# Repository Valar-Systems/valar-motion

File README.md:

# Valar Motion — Valar Systems motor controllers

The easiest, fastest, cheapest, and safest way to spin a stepper motor
**wirelessly**. Valar Motion is a family of tiny Wi-Fi stepper controllers built
around a Trinamic **TMC2209** driver — precisely control a motor's distance,
speed, current, and stall behaviour within minutes of unboxing, from any browser,
with no Home Assistant required.

All three boards share the same TMC2209 driver, a synchronous DC/DC converter,
three buttons, end-stop inputs, and a USB-C port for flashing. They differ only
in the microcontroller and — on the 3101 — an onboard magnetic encoder.

| Board | MCU | Radios | Extra | Price |
|-------|-----|--------|-------|-------|
| **VAL3000** | ESP32-C3 | Wi-Fi | — | $34.99 |
| **VAL3100** | ESP32-C6 | Wi-Fi / Thread / Zigbee / Matter / BLE | Status LED | $44.99 |
| **VAL3101** | ESP32-C6 | Wi-Fi / Thread / Zigbee / Matter / BLE | Status LED + AS5600 encoder (closed-loop) | $54.99 |

Buy them at [valarsystems.com](https://valarsystems.com). Sold out? Hit the
"Notify me when available" button — that's the only way we know to make more.

## What's on the board

The board packs a full wireless stepper controller into a footprint that bolts
onto the back of a **NEMA 17** motor (the four mounting holes line up with the
motor face):

- **Espressif ESP32** — Wi-Fi microcontroller with native USB (C3 on the VAL3000;
  C6 with Thread/Zigbee/Matter/BLE on the VAL3100/3101)
- **Trinamic TMC2209** stepper driver — silent StealthChop + sensorless StallGuard
- **5–24 V synchronous DC/DC converter** — efficient on-board regulation from the
  motor supply, no separate logic power needed
- **Three buttons** for manual open / close / Wi-Fi-reset
- **Motor hookup** — the **VAL3100 / VAL3101** ship with a **4-pin screw terminal
  pre-soldered** for the stepper (alongside the JST-XH); the **VAL3000** has the
  **JST-XH** connector (screw terminal included to solder on, or wire directly to
  the pads)
- **Power** — 2.1 × 5.5 mm barrel **and** a 2-pin screw terminal, plus **USB-C**
  for flashing
- **Reverse-polarity protection** on the **VAL3100 / VAL3101** (the VAL3000 has
  none — mind the polarity)

<p align="center">
  
  <br>
  <em>Board anatomy (VAL3000 shown; the VAL3100/3101 share the same layout on an ESP32-C6).</em>
</p>

## Quick start

Setup takes about three minutes:

1. Connect any bipolar (4-wire) stepper motor.
2. Connect a 12–24 V, 2 A+ power supply (2.1 × 5.5 mm barrel, **center positive**).
3. Press one of the buttons — the motor starts and stops.

That's it. When you're ready to customize, plug in USB-C and flash a build below.

> **⚠️ VAL3000 only:** the VAL3000 has **no reverse-polarity protection** —
> double-check your supply is center-positive before powering on. The
> VAL3100 / VAL3101 add reverse-polarity protection.

## Flash a board (the fast way)

The board ships bare. Grab the prebuilt binary for your board from the
[latest release](../../releases/latest) and flash it from your browser at
[web.esphome.io](https://web.esphome.io) with a USB-C cable — no toolchain, no
soldering, no Home Assistant required. On first boot the board makes its own
Wi-Fi hotspot; connect, join it to your network, and control it from any
browser. It's discoverable in Home Assistant over the ESPHome API too.

> First-time flashing note: the USB-C port connects straight to the ESP32 (USB
> CDC — no USB-to-UART bridge). If the board isn't detected on a brand-new unit,
> enter download mode manually: **hold** BOOT, **tap** RESET, then **release**
> BOOT. After the first upload this is automatic.

## Build from source

```bash
python3 -m venv venv && source venv/bin/activate
pip install esphome
cp secrets.example.yaml secrets.yaml     # not needed for a bare flash

esphome compile boards/val3100/val3100.yaml
# → factory image at:
#   boards/val3100/.esphome/build/val3100/.pioenvs/val3100/firmware.factory.bin
```

Swap `val3100` for `val3000` or `val3101`. CI
(`.github/workflows/build-firmware.yml`) builds all three on every push and
attaches `*.factory.bin` / `*.ota.bin` to tagged releases.

## Firmware updates (OTA)

Boards can update themselves over Wi-Fi — no computer needed — by fetching the
newest release asset for their board. **Release asset names are an API**: keep
`val3000.factory.bin`, `val3100.ota.bin`, etc. stable so units already in the
field keep updating after any repo move. See `docs/MIGRATION.md`.

## Detailed features

### Trinamic TMC2209 + StallGuard

The TMC2209 is one of the best stepper drivers on the market — feature-rich yet
affordable, with silent StealthChop operation and sensorless stall detection.
**StallGuard** stops the motor whenever the load exceeds a threshold you set — no
limit switches needed — which makes the board safe for curtains, windows, blinds,
and anything that could pinch or jam. The driver is controlled over a single-wire
UART, so speed, current, microstepping, and stall sensitivity are all tunable
live from the web UI.

### Flexible motor connector

Connect a motor three ways: the on-board 4-pin JST-XH plug, the included 4-pin
screw terminal (solder it to the exposed pins), or by soldering the motor wires
directly to the board.

### USB-C + three buttons

Flash firmware and monitor serial over USB-C — no programmer needed. Three
on-board buttons give physical open / close control plus a Wi-Fi reset, handy for
products built on the board (our Ropener curtain opener uses exactly this).

## Repository layout

```
valar-motion/
├── boards/
│   ├── val3000/val3000.yaml   # ESP32-C3 pin map + substitutions
│   ├── val3100/val3100.yaml   # ESP32-C6 + status LED
│   └── val3101/val3101.yaml   # ESP32-C6 + status LED + AS5600 encoder
├── common/
│   └── valar-core.yaml        # shared, board-independent behaviour
├── hardware/                  # PCB, schematics, libraries (per board)
├── docs/                      # datasheets, guides, media
└── .github/workflows/         # CI: builds a factory + OTA bin per board
```

The important idea: **behaviour lives in `common/valar-core.yaml`**, which every
board pulls in as a package. Each `boards/<board>/<board>.yaml` is a thin wrapper
that only sets that board's chip, GPIO pin map, and OTA asset name. Change the
core once and all three boards inherit it.

## Hardware & documentation

- **Hardware guide:** [`docs/hardware-guide.md`](docs/hardware-guide.md) — power/voltage/current/heat, driving the TMC2209 (UART vs STEP/DIR), and mounting to a NEMA 17
- **PCB / KiCad sources:** [`hardware/val3000`](hardware/val3000),
  [`hardware/val3100`](hardware/val3100) (the VAL3101 uses the VAL3100 board with
  the AS5600 encoder populated — see [`hardware/val3101`](hardware/val3101))
- **Schematic (PDF):** [`docs/val3000/schematic.pdf`](docs/val3000/schematic.pdf)
- **Trinamic book (PDF):** [`docs/val3000/Trinamic_Book_V4.pdf`](docs/val3000/Trinamic_Book_V4.pdf) — in-depth guide to Trinamic drivers
- **TMC2209 datasheet:** [analog.com](https://www.analog.com/media/en/technical-documentation/data-sheets/tmc2209_datasheet_rev1.09.pdf)

## Applications

This repo is the **board firmware**. Products built on these boards live in their
own repos and layer their behaviour on top of `common/valar-core.yaml` — e.g.
[The Ropener](https://github.com/Valar-Systems/Ropener), a smart curtain opener,
which adds cover/position logic and homing on the same boards.

## License

Licensed under the [CERN Open Hardware Licence Version 2 — Strongly Reciprocal](LICENSE).

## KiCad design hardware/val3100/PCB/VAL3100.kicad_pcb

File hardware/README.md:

# Hardware

PCB source, schematics, and libraries for each board we sell, one folder per board.

    hardware/val3000/   # ESP32-C3 board — KiCad source + libraries (from the old VAL3000 repo)
    hardware/val3100/   # ESP32-C6 board — KiCad source + libraries (from the old VAL3100 repo)
    hardware/val3101/   # ESP32-C6 + AS5600 — SAME PCB as val3100 (see below)

Board-specific documentation (schematic PDFs, datasheets, media) lives under
`docs/<board>/` — e.g. `docs/val3000/`.

## VAL3101 shares the VAL3100 board

The **VAL3101 is not a separate PCB** — it is the VAL3100 board with the AS5600
magnetic encoder **populated**. The VAL3100 layout already carries the AS5600
footprint and its I²C routing; on a plain VAL3100 the chip is simply left
unstuffed. Populate it (plus the shaft magnet) and it becomes a VAL3101.

So `hardware/val3101/` intentionally has no separate KiCad project — use
`hardware/val3100/`. The encoder's I²C pins, read from that schematic, are
**SDA = GPIO14, SCL = GPIO15** (see `boards/val3101/val3101.yaml`).

## What was migrated

Only real design source was brought over: `.kicad_pcb`, `.kicad_sch`,
`.kicad_pro`, vendor `Libraries/`, and fabrication config. KiCad auto-save
`*-backups/` archives, project-local `.kicad_prl` state, lock files, and caches
were intentionally left out (and are `.gitignore`d) — they remain in the
original board repos, which are archived rather than deleted.

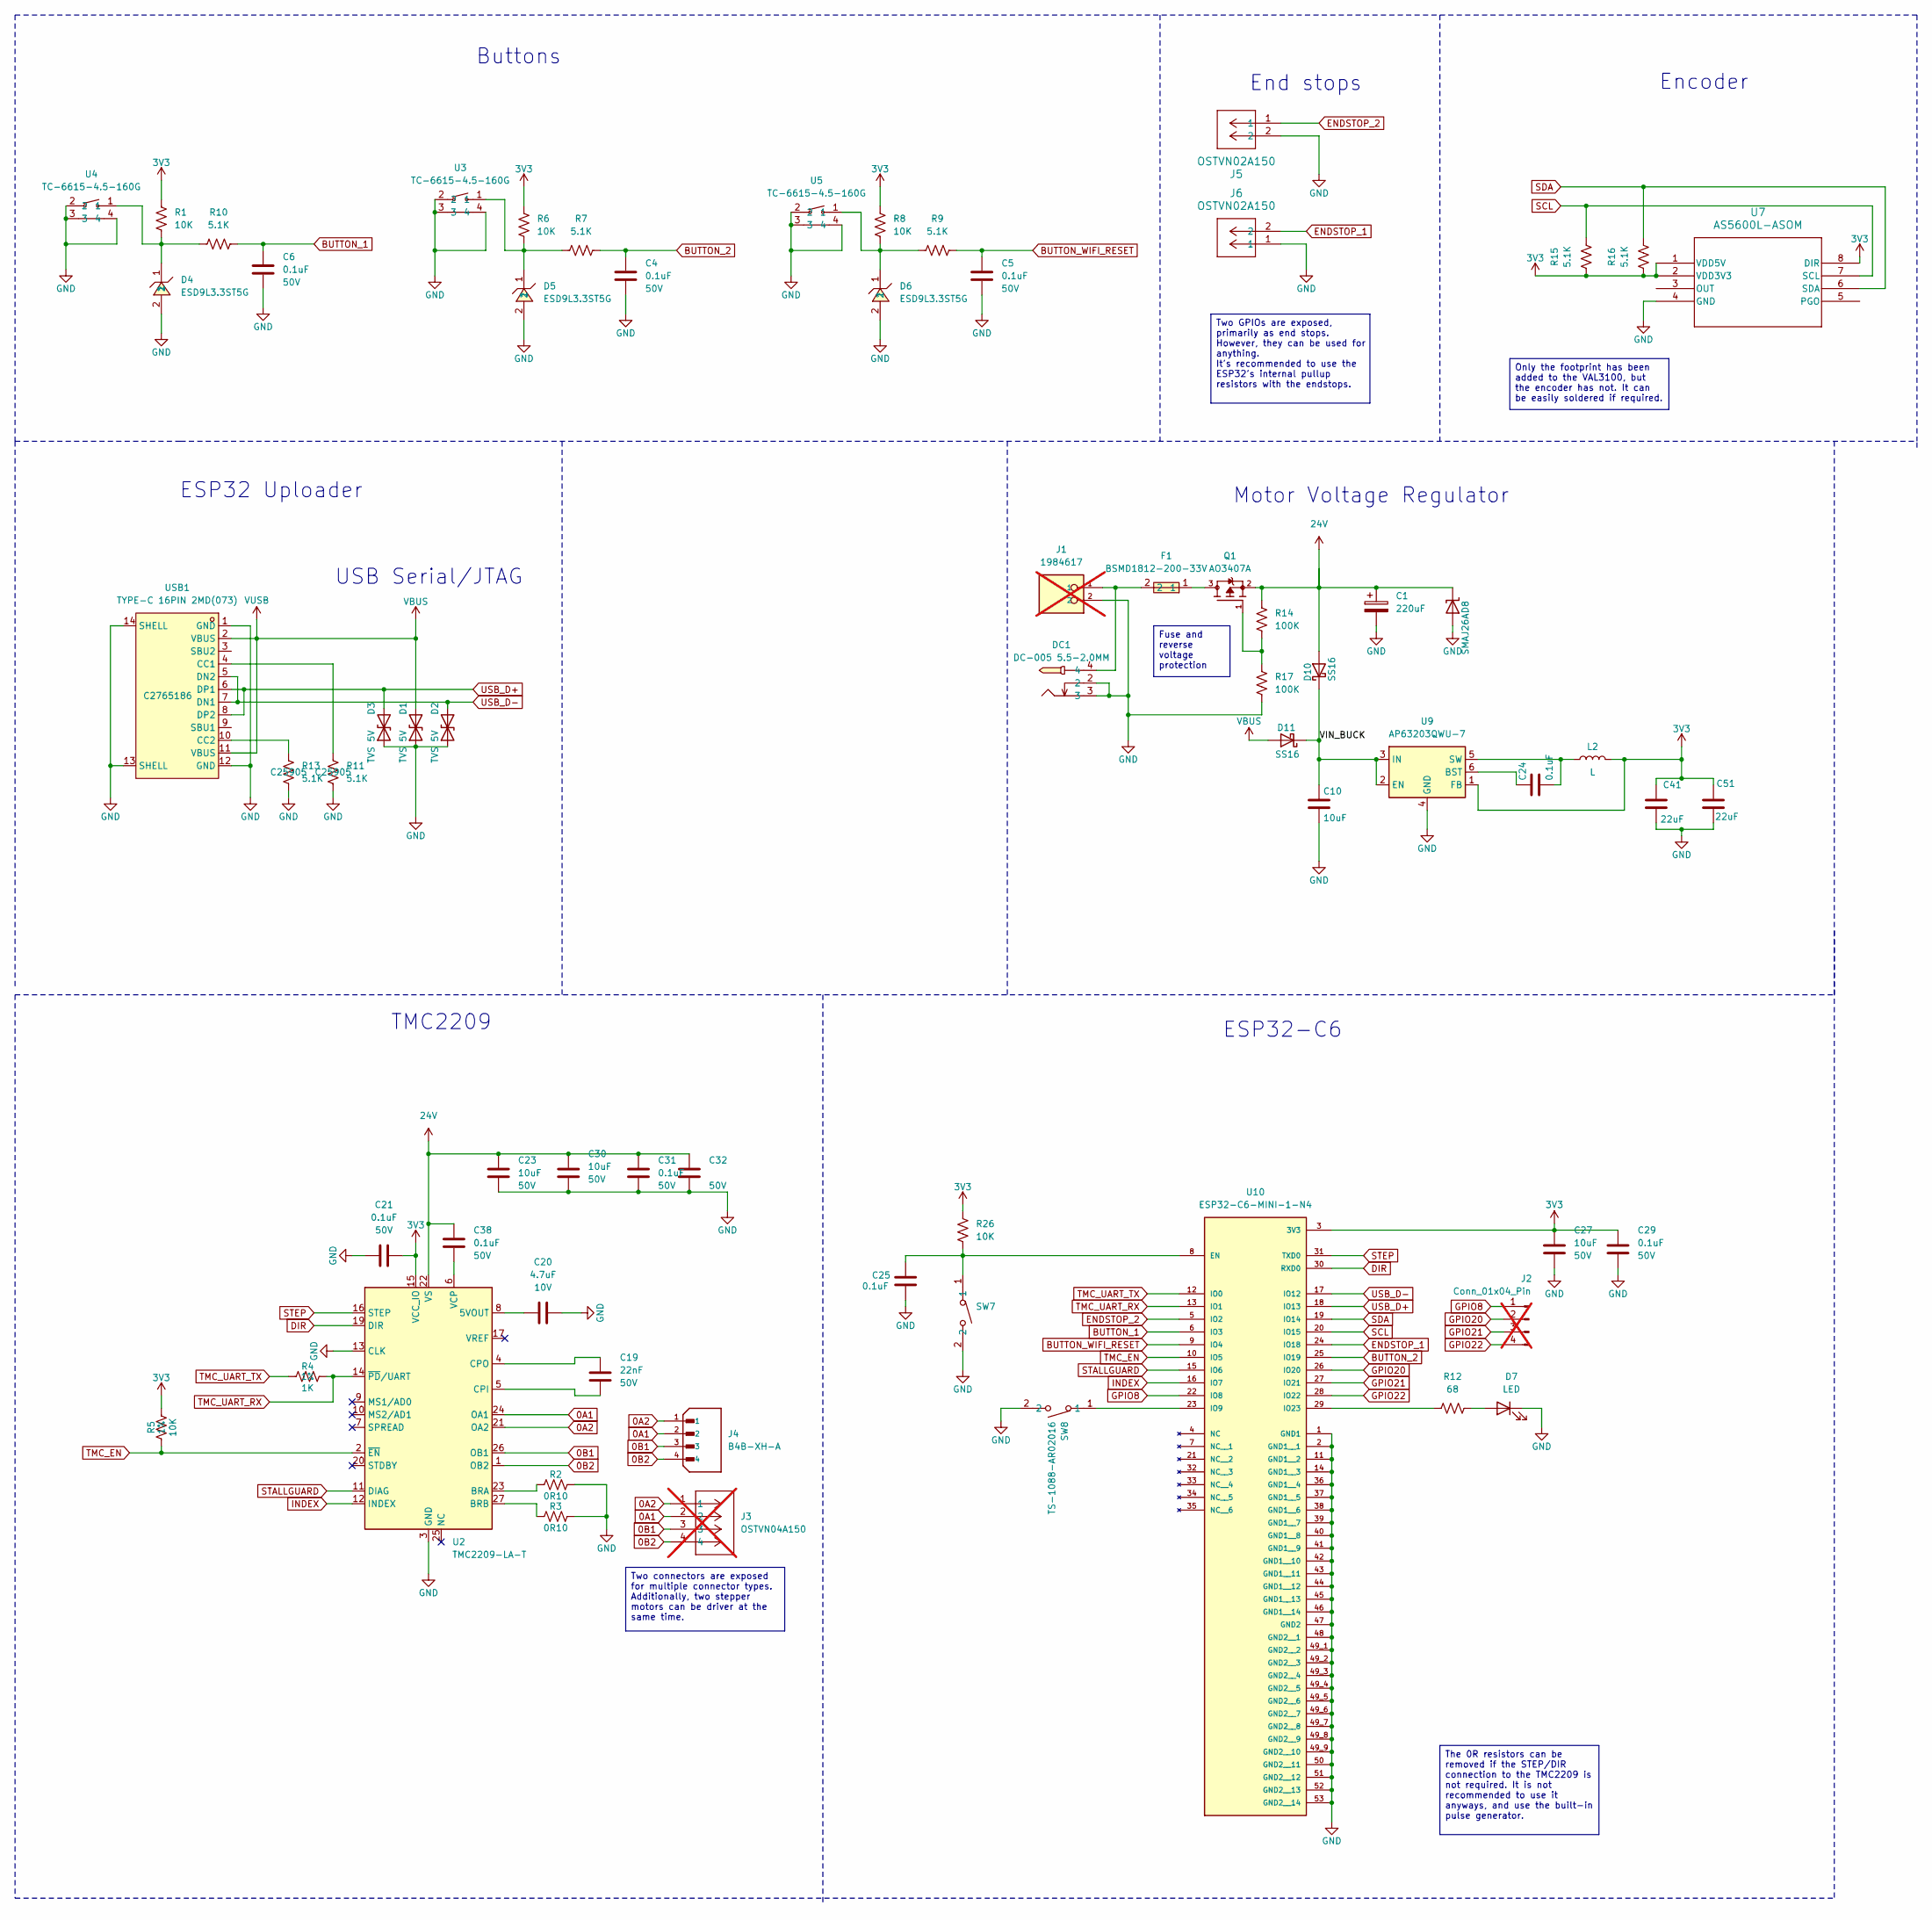
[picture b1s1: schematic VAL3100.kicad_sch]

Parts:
C1: 220uF; CAP-SMD_BD10.0-L10.3-W10.3-LS11.3-FD; Voltage 50V; LCSC C98743
C4, C5, C6, C21, C24, C29, C31, C32, C38: 0.1uF; C_0402_1005Metric; Voltage 50V; Tolerance 10%; LCSC C77020
C10: 10uF; C_0805_2012Metric; Voltage 50V; Tolerance 10%; LCSC C440198
C19: 22nF; C_0402_1005Metric; Voltage 50V; Tolerance 10%; LCSC C1532
C20: 4.7uF; C_0402_1005Metric; Voltage 10V; Tolerance 10%; LCSC C23733
C23, C27, C30: 10uF; C_0805_2012Metric; Voltage 50V; Tolerance 20%; LCSC C440198
C25: 0.1uF; C_0402_1005Metric; Voltage 50V; LCSC C77020
C41, C51: 22uF; C_0603_1608Metric; Voltage 10V; Tolerance 20%; LCSC C86295
D1, D2, D3: SOD-523_BSD5C051L; D_SOD-523; MPN BSD5C051L; LCSC C151983
D4, D5, D6: ESD9L3.3ST5G; SOD-923_L0.8-W0.6-LS1.0-RD; LCSC C233387
D7: LED; LED_0603_1608Metric; LCSC C2286
D8: SMAJ26A; D_SMA; MPN SMAJ26A-TR; LCSC C132945
D10, D11: SS16; D_SMA; MPN SS16; LCSC C22452
DC1: DC-005 5.5-2.0MM; DC-IN-TH_DC-005-5.5-2.0; LCSC C16214
F1: BSMD1812-200-33V; F1812; LCSC C7433877
J1: 1984617; PHOENIX_1984617; PARTREV 22.08.2018; LCSC C695629; not fitted
J2: Conn_01x04_Pin; PinHeader_1x04_P2.54mm_Vertical; not fitted
J3: OSTVN04A150; CONN_OSTVN04A150_OST; JLCPCB C918122; not fitted
J4: B4B-XH-A; JST_B4B-XH-A; PARTREV 7/4/21; LCSC C144395
J5, J6: OSTVN02A150; CONN_OSTVN02A150_OST
L2: L; IND-SMD_L3.0-W3.0_FNR30XXS; LCSC C48020
Q1: AO3407A; SOT95P280X125-3N; PARTREV 5; LCSC C15155
R1, R5, R6, R8, R26: 10K; R_0402_1005Metric; LCSC C25744
R2, R3: 0R10; C_0805_2012Metric; LCSC C2074770
R4: 1K; R_0402_1005Metric; LCSC C11702
R7, R9, R10, R11, R13, R15, R16: 5.1K; R_0402_1005Metric; LCSC C25905
R12: 68; R_0402_1005Metric; LCSC C25131
R14, R17: 100K; R_0402_1005Metric; LCSC C25741
SW7, SW8: TS-1088-AR02016; SW-SMD_L3.9-W3.0-P4.45; LCSC C720477
U2: TMC2209-LA-T; VQFN-28-1EP_5x5mm_P0.5mm_EP3.7x3.7mm_ThermalVias; LCSC C2150710
U3, U4, U5: TC-6615-4.5-160G; KEY-TH_TC-6615-4.5-160G; LCSC C6575012
U7: AS5600L-ASOM; AS5600L-ASOM_AMS; LCSC C2153666
U9: AP63203QWU-7; TSOT-23-6; LCSC C780769
U10: ESP32-C6-MINI-1-N4; XCVR_ESP32-C6-MINI-1-N4; PARTREV 1.0; DigiKey_Part_Number 1965-ESP32-C6-MINI-1-N4CT-ND
USB1: TYPE-C 16PIN 2MD(073); USB-C-SMD_TYPE-C-6PIN-2MD-073; LCSC C2765186

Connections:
0A1: J3.2, J4.2, U2.24 (OA1)
0A2: J3.1, J4.1, U2.21 (OA2)
0B1: J3.3, J4.3, U2.26 (OB1)
0B2: J3.4, J4.4, U2.1 (OB2)
3V3: C21.2, C27.1, C29.1, C41.2, C51.2, L2.2, R1.1, R5.2, R6.1, R8.1, R15.1, R16.1, R26.1, U2.15 (VCC_IO), U7.1 (VDD5V), U7.2 (VDD3V3), U7.8 (DIR), U9.1 (FB), U10.3 (3V3)
24V: C1.1, C23.1, C30.1, C31.2, C32.2, C38.2, D8.1 (K), D10.2 (A), Q1.2, R14.2, U2.22 (VS), U2.28 (VS)
/VIN_BUCK: C10.1, D10.1 (K), D11.1 (K), U9.2 (EN), U9.3 (IN)
BUTTON_1: C6.2, R10.2, U10.6 (IO3)
BUTTON_2: C4.2, R7.2, U10.25 (IO19)
BUTTON_WIFI_RESET: C5.2, R9.2, U10.9 (IO4)
DIR: U2.19 (DIR), U10.30 (RXD0)
ENDSTOP_1: J6.2, U10.24 (IO18)
ENDSTOP_2: J5.1, U10.5 (IO2)
GND: C1.2, C4.1, C5.1, C6.1, C10.2, C20.2, C21.1, C23.2, C25.2, C27.2, C29.2, C30.2, C31.1, C32.1, C41.1, C51.1, D1.1 (A1), D2.1 (A1), D3.1 (A1), D4.2, D5.2, D6.2, D7.1 (K), D8.2 (A), DC1.2, DC1.3, J1.2, J5.2, J6.1, R2.2, R3.2, R11.2, R13.1, R17.1, SW7.2, SW8.2, U2.3 (GND), U2.13 (CLK), U2.18 (GND), U2.29 (GND), U3.2, U3.3, U3.4, U4.2, U4.3, U4.4, U5.2, U5.3, U5.4, U7.4 (GND), U9.4 (GND), U10.1 (GND1), U10.2 (GND1__1), U10.11 (GND1__2), U10.14 (GND1__3), U10.36 (GND1__4), U10.37 (GND1__5), U10.38 (GND1__6), U10.39 (GND1__7), U10.40 (GND1__8), U10.41 (GND1__9), U10.42 (GND1__10), U10.43 (GND1__11), U10.44 (GND1__12), U10.45 (GND1__13), U10.46 (GND1__14), U10.47 (GND2), U10.48 (GND2__1), U10.49_1 (GND2__2), U10.49_2 (GND2__3), U10.49_3 (GND2__4), U10.49_4 (GND2__5), U10.49_5 (GND2__6), U10.49_6 (GND2__7), U10.49_7 (GND2__8), U10.49_8 (GND2__9), U10.49_9 (GND2__10), U10.50 (GND2__11), U10.51 (GND2__12), U10.52 (GND2__13), U10.53 (GND2__14), USB1.1 (GND), USB1.12 (GND), USB1.13 (SHELL), USB1.14 (SHELL); also elsewhere on the board
GPIO8: J2.1, U10.22 (IO8)
GPIO20: J2.2, U10.26 (IO20)
GPIO21: J2.3, U10.27 (IO21)
GPIO22: J2.4, U10.28 (IO22)
INDEX: U2.12 (INDEX), U10.16 (IO7)
unnamed: D4.1, R1.2, R10.1, U4.1
unnamed: D5.1, R6.2, R7.1, U3.1
unnamed: D6.1, R8.2, R9.1, U5.1
unnamed: D7.2 (A), R12.2
unnamed: DC1.4, F1.2, J1.1
unnamed: F1.1, Q1.3
unnamed: Q1.1, R14.1, R17.2
unnamed: C20.1, U2.8 (5VOUT)
unnamed: R2.1, U2.23 (BRA)
unnamed: R3.1, U2.27 (BRB)
unnamed: C19.2, U2.5 (CPI)
unnamed: C19.1, U2.4 (CPO)
unnamed: C38.1, U2.6 (VCP)
unnamed: C24.1, U9.6 (BST)
unnamed: C24.2, L2.1, U9.5 (SW)
unnamed: C25.1, R26.2, SW7.1, U10.8 (EN)
unnamed: SW8.1, U10.23 (IO9)
unnamed: R12.1, U10.29 (IO23)
unnamed: R11.1, USB1.4 (CC1)
unnamed: R13.2, USB1.10 (CC2)
SCL: R15.2, U7.7 (SCL), U10.20 (IO15)
SDA: R16.2, U7.6 (SDA), U10.19 (IO14)
STALLGUARD: U2.11 (DIAG), U10.15 (IO6)
STEP: U2.16 (STEP), U10.31 (TXD0)
TMC_EN: R5.1, U2.2 (~EN), U10.10 (IO5)
TMC_UART_RX: R4.2, U2.14 (~PD/UART), U10.13 (IO1)
TMC_UART_TX: R4.1, U10.12 (IO0)
USB_D+: D3.2 (A2), U10.18 (IO13), USB1.6 (DP1), USB1.8 (DP2)
USB_D-: D2.2 (A2), U10.17 (IO12), USB1.5 (DN2), USB1.7 (DN1)
VBUS: D1.2 (A2), D11.2 (A), USB1.2 (VBUS), USB1.11 (VBUS)

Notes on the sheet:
Motor Voltage Regulator
ESP32-C6
Buttons
TMC2209
ESP32 Uploader
End stops
Encoder
USB Serial/JTAG
The 0R resistors can be removed if the STEP/DIR connection to the TMC2209 is not required. It is not recommended to use it anyways, and use the built-in pulse generator.
Two connectors are exposed for multiple connector types. Additionally, two stepper motors can be driver at the same time.
Only the footprint has been added to the VAL3100, but the encoder has not. It can be easily soldered if required.
Two GPIOs are exposed, primarily as end stops. However, they can be used for anything. It's recommended to use the ESP32's internal pullup resistors with the endstops.
Fuse and reverse voltage protection

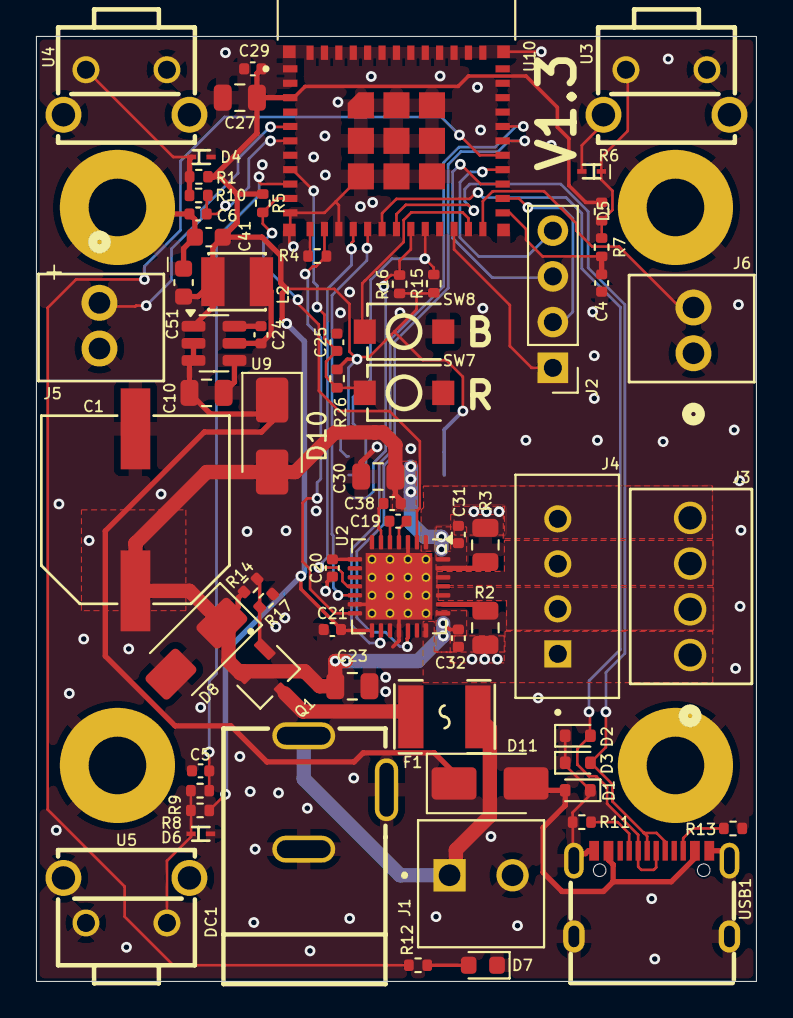
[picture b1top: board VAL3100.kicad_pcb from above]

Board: 4 copper layers, 40.0 x 52.5 mm, 71 parts (1 on the bottom side), 49 nets.

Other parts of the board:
H1, H2, H3, H4: MountingHole_3.2mm_M3_Pad

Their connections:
GND: H1.1, H2.1, H3.1, H4.1; also elsewhere on the board

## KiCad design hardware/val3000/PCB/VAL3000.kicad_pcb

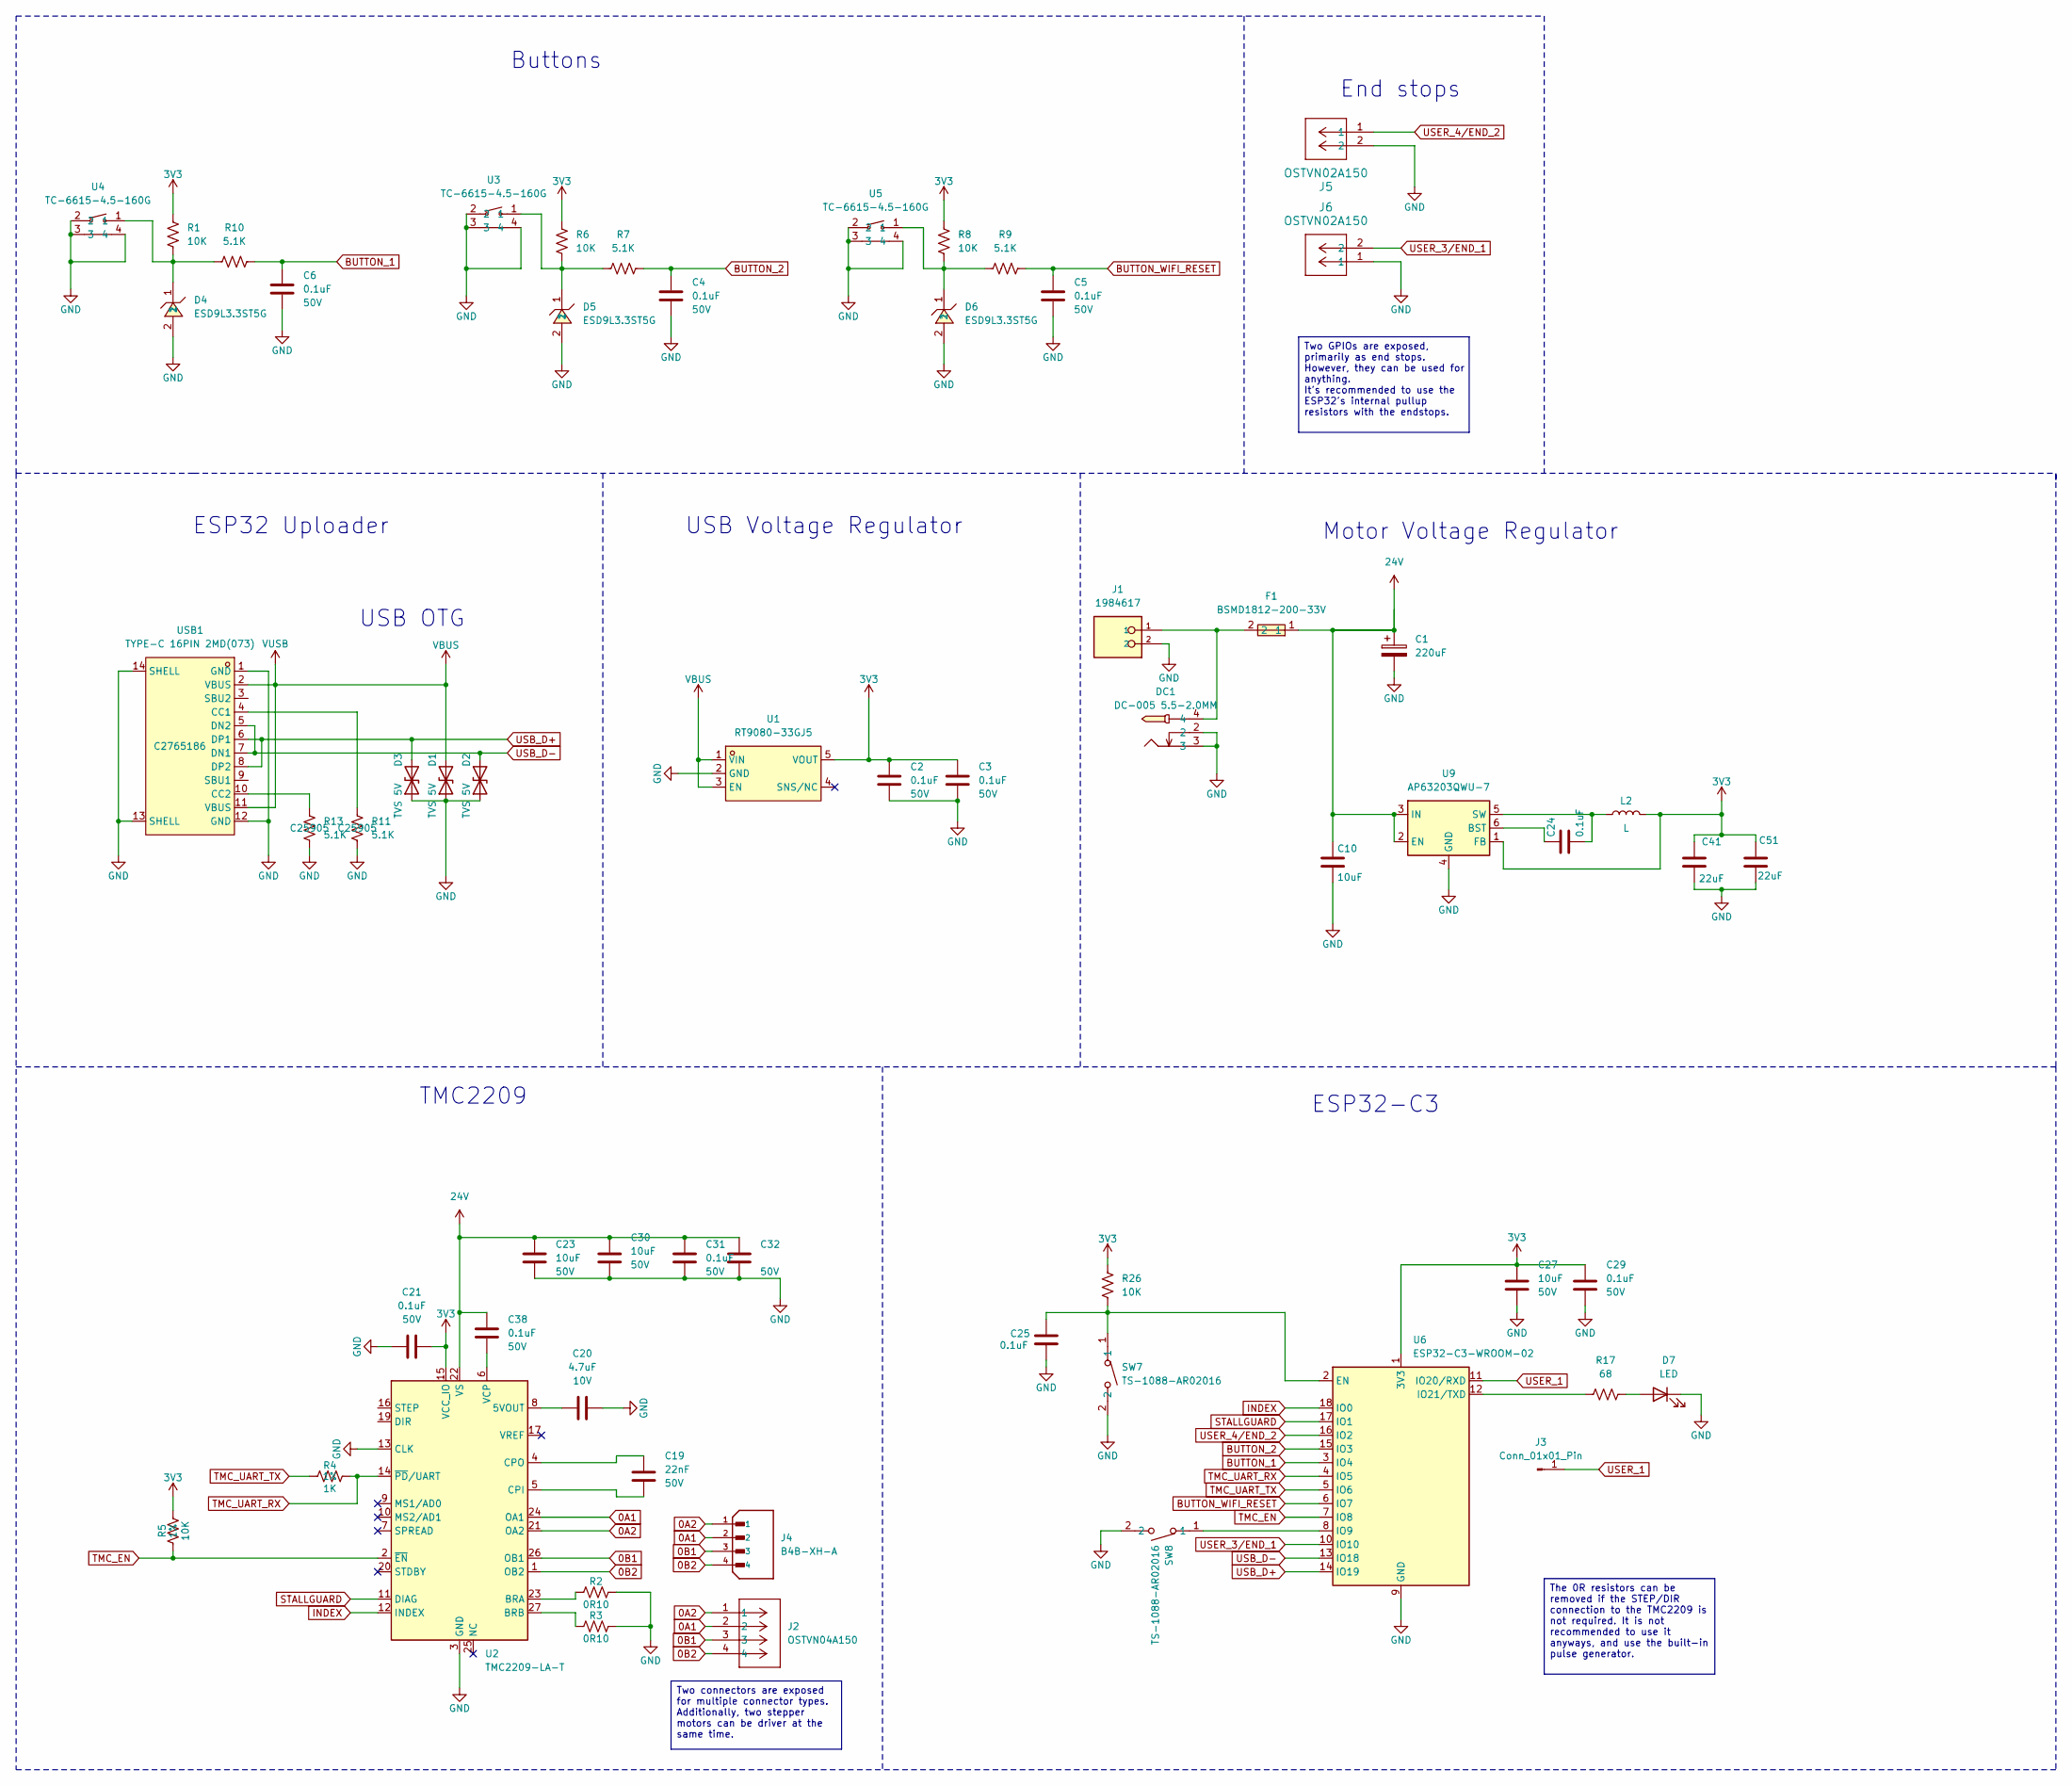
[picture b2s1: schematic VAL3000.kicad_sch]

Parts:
C1: 220uF; CAP-SMD_BD10.0-L10.3-W10.3-LS11.3-FD; Voltage 50V; LCSC C98743
C2, C3, C4, C5, C6, C21, C24, C29, C31, C32, C38: 0.1uF; C_0402_1005Metric; Voltage 50V; Tolerance 10%; LCSC C77020
C10: 10uF; C_0805_2012Metric; Voltage 50V; Tolerance 10%; LCSC C440198
C19: 22nF; C_0402_1005Metric; Voltage 50V; Tolerance 10%; LCSC C1532
C20: 4.7uF; C_0402_1005Metric; Voltage 10V; Tolerance 10%; LCSC C23733
C23, C27, C30: 10uF; C_0805_2012Metric; Voltage 50V; Tolerance 20%; LCSC C440198
C25: 0.1uF; C_0402_1005Metric; Voltage 50V; LCSC C77020
C41, C51: 22uF; C_0603_1608Metric; Voltage 10V; Tolerance 20%; LCSC C86295
D1, D2, D3: SOD-523_BSD5C051L; D_SOD-523; MPN BSD5C051L; LCSC C151983
D4, D5, D6: ESD9L3.3ST5G; SOD-923_L0.8-W0.6-LS1.0-RD; LCSC C233387
D7: LED; LED_0603_1608Metric; LCSC C2286
DC1: DC-005 5.5-2.0MM; DC-IN-TH_DC-005-5.5-2.0; LCSC C16214
F1: BSMD1812-200-33V; F1812; LCSC C7433877
J1: 1984617; PHOENIX_1984617; PARTREV 22.08.2018; LCSC C695629
J2: OSTVN04A150; CONN_OSTVN04A150_OST; JLCPCB C918122
J3: Conn_01x01_Pin
J4: B4B-XH-A; JST_B4B-XH-A; PARTREV 7/4/21; LCSC C144395
J5, J6: OSTVN02A150; CONN_OSTVN02A150_OST
L2: L; IND-SMD_L3.0-W3.0_FNR30XXS; LCSC C48020
R1, R5, R6, R8, R26: 10K; R_0402_1005Metric; LCSC C25744
R2, R3: 0R10; C_0805_2012Metric; LCSC C2074770
R4: 1K; R_0402_1005Metric; LCSC C11702
R7, R9, R10, R11, R13: 5.1K; R_0402_1005Metric; LCSC C25905
R17: 68; R_0402_1005Metric; LCSC C25131
SW7, SW8: TS-1088-AR02016; SW-SMD_L3.9-W3.0-P4.45; LCSC C720477
U1: RT9080-33GJ5; TSOT-23-5_L2.9-W1.6-P0.95-LS2.8-BL; LCSC C841192
U2: TMC2209-LA-T; VQFN-28-1EP_5x5mm_P0.5mm_EP3.7x3.7mm_ThermalVias; LCSC C2150710
U3, U4, U5: TC-6615-4.5-160G; KEY-TH_TC-6615-4.5-160G; LCSC C6575012
U6: ESP32-C3-WROOM-02; LCSC C2934560
U9: AP63203QWU-7; TSOT-23-6; LCSC C780769
USB1: TYPE-C 16PIN 2MD(073); USB-C-SMD_TYPE-C-6PIN-2MD-073; LCSC C2765186

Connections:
0A1: J2.2, J4.2, U2.24 (OA1)
0A2: J2.1, J4.1, U2.21 (OA2)
0B1: J2.3, J4.3, U2.26 (OB1)
0B2: J2.4, J4.4, U2.1 (OB2)
3V3: C2.2, C3.2, C21.2, C27.1, C29.1, C41.2, C51.2, L2.2, R1.1, R5.2, R6.1, R8.1, R26.1, U1.5 (VOUT), U2.15 (VCC_IO), U6.1 (3V3), U9.1 (FB)
24V: C1.1, C10.1, C23.1, C30.1, C31.2, C32.2, C38.2, F1.1, U2.22 (VS), U2.28 (VS), U9.2 (EN), U9.3 (IN)
BUTTON_1: C6.2, R10.2, U6.3 (IO4)
BUTTON_2: C4.2, R7.2, U6.15 (IO3)
BUTTON_WIFI_RESET: C5.2, R9.2, U6.6 (IO7)
GND: C1.2, C2.1, C3.1, C4.1, C5.1, C6.1, C10.2, C20.2, C21.1, C23.2, C25.2, C27.2, C29.2, C30.2, C31.1, C32.1, C41.1, C51.1, D1.1 (A1), D2.1 (A1), D3.1 (A1), D4.2, D5.2, D6.2, D7.1 (K), DC1.2, DC1.3, J1.2, J5.2, J6.1, R2.2, R3.2, R11.2, R13.1, SW7.2, SW8.2, U1.2 (GND), U2.3 (GND), U2.13 (CLK), U2.18 (GND), U2.29 (GND), U3.2, U3.3, U3.4, U4.2, U4.3, U4.4, U5.2, U5.3, U5.4, U6.9 (GND), U6.19 (GND), U9.4 (GND), USB1.1 (GND), USB1.12 (GND), USB1.13 (SHELL), USB1.14 (SHELL); also elsewhere on the board
INDEX: U2.12 (INDEX), U6.18 (IO0)
unnamed: D4.1, R1.2, R10.1, U4.1
unnamed: D5.1, R6.2, R7.1, U3.1
unnamed: D6.1, R8.2, R9.1, U5.1
unnamed: D7.2 (A), R17.2
unnamed: DC1.4, F1.2, J1.1
unnamed: C20.1, U2.8 (5VOUT)
unnamed: R2.1, U2.23 (BRA)
unnamed: R3.1, U2.27 (BRB)
unnamed: C19.2, U2.5 (CPI)
unnamed: C19.1, U2.4 (CPO)
unnamed: C38.1, U2.6 (VCP)
unnamed: C25.1, R26.2, SW7.1, U6.2 (EN)
unnamed: SW8.1, U6.8 (IO9)
unnamed: R17.1, U6.12 (IO21/TXD)
unnamed: C24.1, U9.6 (BST)
unnamed: C24.2, L2.1, U9.5 (SW)
unnamed: R11.1, USB1.4 (CC1)
unnamed: R13.2, USB1.10 (CC2)
STALLGUARD: U2.11 (DIAG), U6.17 (IO1)
TMC_EN: R5.1, U2.2 (~EN), U6.7 (IO8)
TMC_UART_RX: R4.2, U2.14 (~PD/UART), U6.4 (IO5)
TMC_UART_TX: R4.1, U6.5 (IO6)
USB_D+: D3.2 (A2), U6.14 (IO19), USB1.6 (DP1), USB1.8 (DP2)
USB_D-: D2.2 (A2), U6.13 (IO18), USB1.5 (DN2), USB1.7 (DN1)
USER_1: J3.1 (Pin_1_1), U6.11 (IO20/RXD)
USER_3/END_1: J6.2, U6.10 (IO10)
USER_4/END_2: J5.1, U6.16 (IO2)
VBUS: D1.2 (A2), U1.1 (VIN), U1.3 (EN), USB1.2 (VBUS), USB1.11 (VBUS)

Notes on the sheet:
Motor Voltage Regulator
ESP32-C3
Buttons
TMC2209
ESP32 Uploader
End stops
USB Voltage Regulator
USB OTG
The 0R resistors can be removed if the STEP/DIR connection to the TMC2209 is not required. It is not recommended to use it anyways, and use the built-in pulse generator.
Two connectors are exposed for multiple connector types. Additionally, two stepper motors can be driver at the same time.
Two GPIOs are exposed, primarily as end stops. However, they can be used for anything. It's recommended to use the ESP32's internal pullup resistors with the endstops.

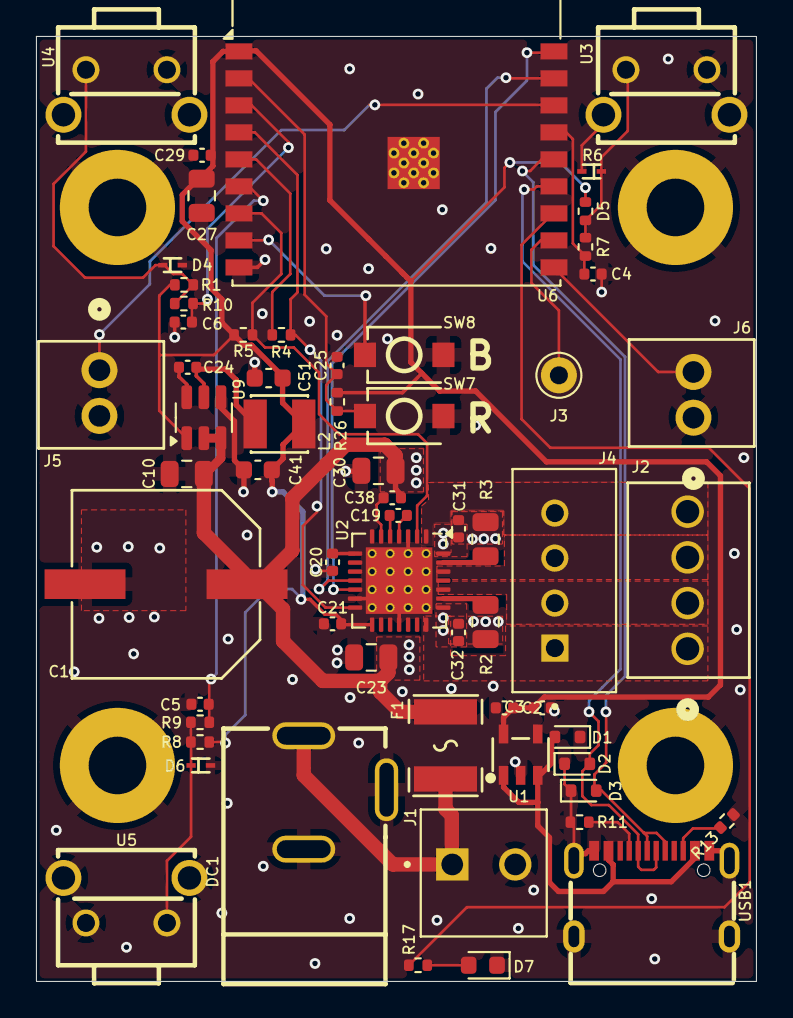
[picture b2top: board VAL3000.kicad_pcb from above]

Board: 4 copper layers, 40.0 x 52.5 mm, 65 parts (0 on the bottom side), 39 nets.

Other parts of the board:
H1, H2, H3, H4: MountingHole_3.2mm_M3_Pad

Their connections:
GND: H1.1, H2.1, H3.1, H4.1; also elsewhere on the board
